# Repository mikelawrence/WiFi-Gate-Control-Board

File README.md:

# WiFi Gate Controller Board

This board performs the same functions as my [WiFi Gate Controller](https://github.com/mikelawrence/WiFi-Gate-Controller), which was designed to add WiFi and Home Assistant control to an existing US Automation Gate Opener board, while providing motor control and standard gate inputs. This board will replace a US Automation Gate Opener board. All inputs are now generalized and also support 10k resistor monitoring for safety devices like edge or photoelectric inputs.

This PCB design uses my custom libraries available here [Mike's KiCad Libraries](https://github.com/mikelawrence/KiCad-Libraries).

This PCB was designed with [KiCad 5.1.4](http://kicad.org).

_Note: Multiple ICs and Modules have exposed pads on the bottom which requires either a reflow oven or hot air to solder properly._

For Bill of Materials generation I use my version of [KiBoM](https://github.com/mikelawrence/KiBoM) forked from [SchrodingersGat](https://github.com/SchrodingersGat/KiBoM).

## Status

* Rev 1.1 PCB was built by and received from PCBWay.
  * This is a 4 layer PCB using 2 oz. copper for all layers and is relatively expensive.
  * Board has been assembled with no problems.
  * Motor interface still needs to be tested everything else is good.
  * You can order PCB from [PCBWay](https://www.pcbway.com/project/shareproject/WiFi_Gate_Control_Board_Rev_1_1.html).
  * You can order parts from Mouser using this [shared BOM](https://www.mouser.com/ProjectManager/ProjectDetail.aspx?AccessID=5c81251866).

* Rev 1.0 PCB was built by and received from PCBWay. Testing is complete.
  * PCBWay built the board.
  * I2C interface to TCA6424A, TCA6408A and LPC5024 verified. Reset not connected error found and corrected in Rev 1.1.
  * 12VDC input and reverse polarity protection verified.
  * LED circuitry and power supply verified.
  * All 12 Inputs verified. This includes switch closure and 10k monitoring.
  * All +12V switched outputs verified. Overload tested also.
  * All 2 Normally Open outputs tested.
  * Full-bridge motor control has been tested up to 30A. Far more than needed.
  * Motor current sensing verified. Removed U26 and connected IN input for each half-bridge directly to processor. Needed to set both half-bridges to active low so MIS offset could be measured unloaded.

## Board Preview

## Design

Intended to replace a US Automatic Patriot Board, this board can directly drive a single gate actuator in both directions. Multiple generic inputs are provided on board to make connection to existing standard gate functionality (open, close, pushbutton...) easy. By providing a WiFi connection to a MQTT server this board can be controlled via standard home automation software (Home Assistant).

Board size is 5.50" X 6.25". This board is smaller than the standard size of a US Automatic Patriot Board but matches existing spacer locations.

### Input Power

The main input connector (J12) provides connections to both the battery and motor. This connector is used by both US Automatic and Apollo gate openers. See pinout below.

A 15 Amp fuse protects the entire board. DC input range is 12V nominal (5V - 17V). Idle input power consumption is pretty variable running from 69mW to 1.38W with an average around 179mW. Peak power is during WiFi transmit.

There are two identical power supplies. U1 powers most of the board via 3.3V. U1's power source is either main power (J12) or the USB connector (J1) so the microprocessor can be programmed on the bench without main power. All LEDs on the board are powered by a separate power supply (U21) which can be turned off by the microprocessor. This substantially reduces power consumption

### Board connections

There are nine screw terminal blocks with removable headers on the board used to connect with all gate functions.

| Terminal | Name  | Conn  | Description                            |
| :---:    | :---: | :---: | :---                                   |
| 01       | +12V  | J3    | +12V power, Always on, fused 0.75A     |
| 02       | IN1   | J3    | Input 1 (Radio)                        |
| 03       | IN2   | J3    | Input 2                                |
| 04       | GND   | J3    | Common Ground                          |
| 05       | +12V  | J5    | +12V power, Always on, fused 0.75A     |
| 06       | IN3   | J5    | Input 3                                |
| 07       | IN4   | J5    | Input 4                                |
| 08       | GND   | J5    | Common Ground                          |
| 09       | IN5   | J8    | Input 5                                |
| 10       | GND   | J8    | Common Ground                          |
| 11       | IN6   | J8    | Input 6                                |
| 12       | GND   | J8    | Common Ground                          |
| 13       | IN7   | J4    | Input 7                                |
| 14       | GND   | J4    | Common Ground                          |
| 15       | IN8   | J4    | Input 8                                |
| 16       | GND   | J4    | Common Ground                          |
| 17       | IN9   | J6    | Input 9                                |
| 18       | GND   | J6    | Common Ground                          |
| 19       | IN10  | J6    | Input 10                               |
| 20       | GND   | J6    | Common Ground                          |
| 21       | IN11  | J7    | +12V power, Switched PhotoEye power    |
| 22       | GND   | J7    | Input 11                               |
| 23       | IN12  | J7    | Input 12                               |
| 24       | GND   | J7    | Common Ground                          |
| 25       | +AL   | J9    | +12V power, Switched Alarm power       |
| 26       | GND   | J9    | Common Ground                          |
| 27       | OUT1  | J7    | Output 1, NO switch Output 1           |
| 28       | COM1  | J7    | Common 1, NO switch Output 1           |
| 29       | GND   | J9    | Common Ground                          |
| 30       | +12V  | J9    | +12V power, Switched Output 1 power    |
| 31       | OUT2  | J7    | Output 2, NO switch Output 2           |
| 32       | COM2  | J7    | Common 2, NO switch Output 2           |
| 33       | GND   | J9    | Common Ground                          |
| 34       | +12V  | J9    | +12V power, Switched Output 2 power    |

### Inputs

There are 12 identical physical inputs on this board. Each input can support Normally Open, Normally Closed, and 10k Monitored Normally Open inputs. A Normally Open input is a dry contact that is open when inactive and closed (shorted) when active. A Normally Closed input is the opposite; closed (shorted) when inactive and open when active. A 10k Monitored input is a Normally Open dry contact with a 8k to 10k resistor across the contacts and is normally used for safety inputs. The resistor allows the connections to the contact to be monitored while inactive. The most current efficient input is the Normally Open input which requires no additional current when inactive. The 10k Monitored input requires an additional 49μA and the Normally Closed input requires a 59μA per input while inactive.

Each input is actually a pair of connections: input and ground (negative terminal of battery). This means the ground side is the same (connected) on all inputs and external wiring must take this into account. Each input can be configured for different gate input types in software as shown in the table below.

| Input          | Other Names                  | Type     | Monitored | Action |
| :---           | :---                         | :---:    | :---:     | :---   |
| Push Button    |                              | NO       | No        | Cycle through Open/Stop/Close commands to gate. |
| Close          |                              | NO       | No        | While active, close gate and holds it closed. |
| Open           | Exit, Free Exit              | NO       | No        | While active, opens gate and holds it open. |
| Stop           |                              | NC       | No        | While active, stops the gate and holds it in position. |
| Open PhotoEye  |                              | NO or NC | Yes       | While active, stops an opening gate or prevents gate from opening. |
| Close PhotoEye |                              | NO or NC | Yes       | While active, reverses a closing gate to full open and holds it open. |
| Safety Edge    |                              | NO       | Yes       | When activated, stops and momentarily reverses a moving gate. |
| Safety Loop    | Reverse Loop                 | NO       | Yes       | While active, reverses a closing gate to full open and holds it open. |
| Shadow Loop    | Center Loop, Under Gate Loop | NO       | Yes       | While active, prevents a closed gate from opening, prevents an open gate from closing, or reverses a closing gate to fully open and holds it open. |
| Input 1        |                              | NO or NC | Yes       | Has no gate function. Can be used to monitor say a mailbox door.
| Input 2        |                              | NO or NC | Yes       | Has no gate function.

Look at [Safety Edge Circuit calculations](drawings/Safety Edge Circuit calculations.pdf) for an explanation of how the input circuits with 10k monitoring work.

### Outputs

There are 4 switched power outputs on the board. J7 is used for PhotoEye connections and thus the +12V is switched on only during gate motion. The Alarm +AL is switched to +12V when alarm is active. The +12V on J10 and J11 output connectors are switched based on output settings.

There are several to be defined output settings here.

### SAMD ARM Processor and WiFi Module

The ARM processor and ATWINC1500 WiFi module are wired identical to the MKR1000 Arduino board, thus the Arduino development environment is used for software development and the ATWINC1500 module is directly supported.

## Setup

### Arduino Setup

This board is designed to mimic a [MKR1000](https://store.arduino.cc/usa/arduino-mkr1000) board from Arduino. Make sure the the MKR1000 board is supported by installing. Do this by opening the Board Manager as shown below.

Type in "samd" in the filter edit and you will see several options. Select "Arduino SAMD Boards (32-bits ARM Cortex-M0+)" and install the latest version as shown below.

It will take a few minutes to download and install the board package. Once complete it's time to install the necessary libraries. Start by opening the Library Manager as shown below.

Type in "mqtt" in the filter edit and scroll down until you see "MQTT by Joel Gaehwiler" as shown below.

Once "MQTT" is installed repeat the install for the following libraries.

* WiFi101 by Arduino
* WiFi101OTA by Arduino
* SD by Arduino
* FreeRTOS_SAMD21 by BriscoeTech
* I2C_DMAC version by Martin Lindupp

### Board Setup

The Arduino development environment expects a bootloader in the SAMD ARM processor which will allow programming via USB. The bootloader must be programmed first using a supported programming pod. I used an "Atmel-ICE" pod but there are other options. First make sure you have selected the "Arduino/Genuino MKR1000" board as shown below.

Next select your programmer.

Make sure the board is powered via USB and the programmer is connected to the debug connector then select "Burn Bootloader".

Now the bootloader is programmed it's time to load the "WiFi101 FirmwareUpdater" example. This will update the firmware in the ATWINC1500 module.

Now "Upload" the "WiFi101 FirmwareUpdater" example.

Update the ATWINC1500 module by selecting "WiFi101 Firmware Updater".

Select the latest WINC1501 Model B firmware and click the "Update Firmware" button.

Finally open the "WiFi_Gate_Controller.ino" sketch downloaded from GitHub. Update the necessary defines for your Wireless network and MQTT server settings see the [Code README](code/README.md) for more information. Now upload it just like the "WiFi101 FirmwareUpdater" example. All done!

This project also supports Visual Studio Code. Visual Studio Code supports building Arduino projects and IntelliSense with code completion. The included settings files support my MacOS environment. Just do a search for "Visual Studio Code Arduino" to see how to install.

## Acknowledgments

* [Arduino](www.arduino.cc) kindly develops open source hardware and software which makes writing software for this board and especially the WiFi module easy.
* [Visual Studio Code](https://code.visualstudio.com/) from Microsoft is a great alternative to the Arduino IDE.

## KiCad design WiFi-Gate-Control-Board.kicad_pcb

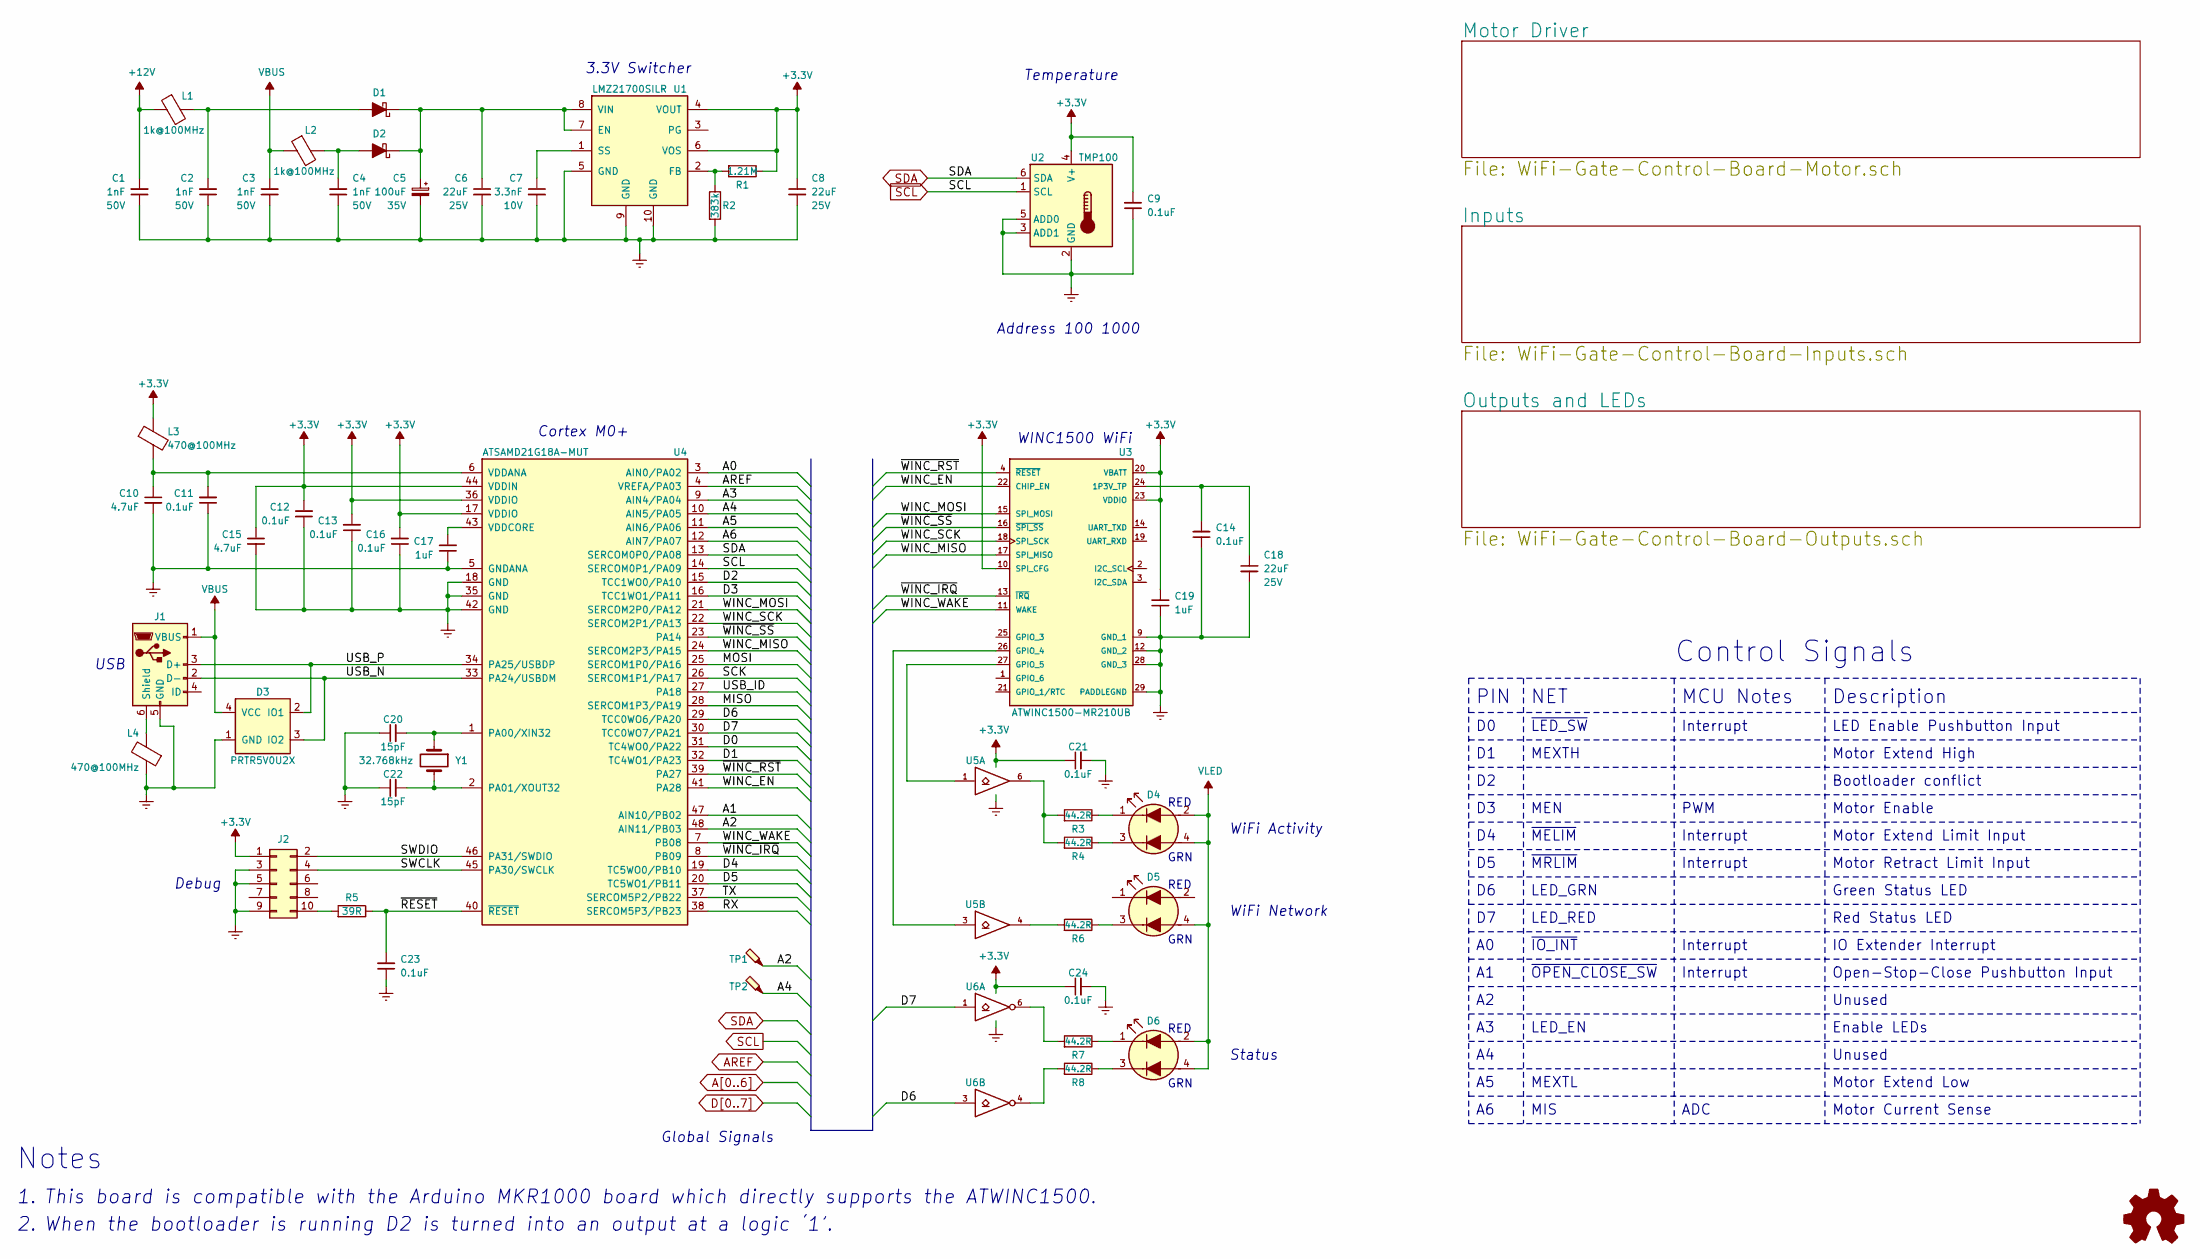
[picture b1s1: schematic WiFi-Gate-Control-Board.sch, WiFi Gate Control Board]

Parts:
C1, C2, C3, C4: 1nF; C_0603_1608Metric; Voltage 50V; Tolerance 10%; Part Number VJ0603Y102KXAAC31
C5: 100uF; CP_Elec_8x10; Voltage 35V; Tolerance 20%; Part Number EMVH350ADA101MHA0G
C6, C8, C18: 22uF; C_0805_2012Metric; Voltage 25V; Tolerance 20%; Part Number TMK212BBJ226MG-TT
C7: 3.3nF; C_0603_1608Metric; Voltage 10V; Tolerance 5%; Part Number VJ0603Y332JXQPW1BC
C9, C11, C12, C13, C14, C16, C21, C23, C24: 0.1uF; C_0603_1608Metric; Voltage 50V; Tolerance 5%; Part Number CC603JRX7R9BB104
C10, C15: 4.7uF; C_0603_1608Metric; Voltage 6.3V; Tolerance 10%; Part Number JMK107BB7475KA-T
C17, C19: 1uF; C_0603_1608Metric; Voltage 50V; Tolerance 10%; Part Number UMK107BJ105KA-T
C20, C22: 15pF; C_0603_1608Metric; Voltage 50V; Tolerance 5%; Part Number 06035A150JAT2A
D1, D2: DFLS130; D_PowerDI-123; Part Number DFLS130LQ
D3: PRTR5V0U2X; SOT-143; Part Number PRTR5V0U2X,215
D4, D5, D6: Red/Green; LED_Avago_PLCC4_3.2x2.8mm_CW; Part Number HSMF-A203-A00J1
J1: USB_B_Micro; USB_Micro-B_Wuerth_614105150721_Vertical_CircularHoles; Part Number 614105150721
J2: Cortex Debug; PinHeader_2x05_P1.27mm_Vertical_SMD; Part Number FTSH-105-01-L-DV-K
L1, L2: 1k@100MHz; L_1206_3216Metric; Part Number BLM31KN102SH1L
L3, L4: 470@100MHz; L_0603_1608Metric; Part Number BLM18PG471SN1D
R1: 1.21M; R_0603_1608Metric; Tolerance 1%; Part Number RC0603FR-071M21L
R2: 383k; R_0603_1608Metric; Tolerance 1%; Part Number ERJ-3EKF3833V
R3, R4, R6, R7, R8: 44.2R; R_0603_1608Metric; Tolerance 1%; Part Number ERJ-3EKF44R2V
R5: 39R; R_0603_1608Metric; Tolerance 1%; Part Number ERJ-3EKF39R0V
TP1, TP2: TestPoint_Probe; TestPoint_Pad_D1.0mm
U1: LMZ21700; Converter_DCDC_Texas-SIL0008E; Part Number LMZ21700SILR
U2: TMP100; SOT-23-6; Part Number TMP100AQDBVRQ1
U3: ATWINC1500-MR210UB; Microchip_ATWINC1500-MR210UB; Part Number ATWINC1500-MR210UB1140
U4: SAMD21G18-M; QFN-48-1EP_7x7mm_P0.5mm_EP5.15x5.15mm; Part Number ATSAMD21G18A-MUT
U5: 74LVC2G07; SOT-23-6; Part Number SN74LVC2G07DBVR
U6: 74LVC2G06; SOT-23-6; Part Number SN74LVC2G06DBVR
Y1: 32.768kHz; Crystal_SMD_Abracon_ABS07-2Pin_3.2x1.5mm; Part Number ABS07-32.768KHZ-9-T

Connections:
+3.3V: C8.1, C9.2, C12.2, C13.2, C15.1, C16.2, C19.2, C21.1, C24.1, J2.1, L3.1, R1.1, U1.4 (VOUT), U1.6 (VOS), U2.4 (V+), U3.10 (SPI_CFG), U3.20 (VBATT), U3.23 (VDDIO), U4.17 (VDDIO), U4.36 (VDDIO), U4.44 (VDDIN), U5.5 (VCC), U6.5 (VCC); also elsewhere on the board
+12V: C1.2, L1.1; also elsewhere on the board
/SWCLK: J2.4, U4.45 (PA30/SWCLK)
/SWDIO: J2.2, U4.46 (PA31/SWDIO)
/USB_N: D3.3 (IO2), J1.2 (D-), U4.33 (PA24/USBDM)
/USB_P: D3.2 (IO1), J1.3 (D+), U4.34 (PA25/USBDP)
/WINC_EN: U3.22 (CHIP_EN), U4.41 (PA28)
/WINC_MISO: U3.17 (SPI_MISO), U4.24 (SERCOM2P3/PA15)
/WINC_MOSI: U3.15 (SPI_MOSI), U4.21 (SERCOM2P0/PA12)
/WINC_SCK: U3.18 (SPI_SCK), U4.22 (SERCOM2P1/PA13)
/WINC_WAKE: U3.11 (WAKE), U4.7 (PB08)
/~RESET~: C23.2, R5.1, U4.40 (~RESET~)
/~WINC_IRQ: U3.13 (~IRQ~), U4.8 (PB09)
/~WINC_RST: U3.4 (~RESET~), U4.39 (PA27)
/~WINC_SS: U3.16 (~SPI_SS~), U4.23 (PA14)
A0: U4.3 (AIN0/PA02); also elsewhere on the board
A1: U4.47 (AIN10/PB02); also elsewhere on the board
A2: TP1.1, U4.48 (AIN11/PB03)
A3: U4.9 (AIN4/PA04); also elsewhere on the board
A4: TP2.1, U4.10 (AIN5/PA05)
A5: U4.11 (AIN6/PA06); also elsewhere on the board
A6: U4.12 (AIN7/PA07); also elsewhere on the board
AREF: U4.4 (VREFA/PA03); also elsewhere on the board
D0: U4.31 (TC4WO0/PA22); also elsewhere on the board
D1: U4.32 (TC4WO1/PA23); also elsewhere on the board
D3: U4.16 (TCC1WO1/PA11); also elsewhere on the board
D4: U4.19 (TC5WO0/PB10); also elsewhere on the board
D5: U4.20 (TC5WO1/PB11); also elsewhere on the board
D6: U4.29 (TCC0WO6/PA20), U6.3
D7: U4.30 (TCC0WO7/PA21), U6.1
GND: C1.1, C2.1, C3.1, C4.1, C5.2, C6.2, C7.2, C8.2, C9.1, C10.2, C11.1, C12.1, C13.1, C14.1, C15.2, C16.1, C17.1, C18.2, C19.1, C20.1, C21.2, C22.1, C23.1, C24.2, D3.1 (GND), J1.5 (GND), J2.3, J2.5, J2.9, L4.1, R2.2, U1.5 (GND), U1.9 (GND), U1.10 (GND), U2.2 (GND), U2.3 (ADD1), U2.5 (ADD0), U3.9 (GND_1), U3.12 (GND_2), U3.28 (GND_3), U3.29 (PADDLEGND), U4.5 (GNDANA), U4.18 (GND), U4.35 (GND), U4.42 (GND), U5.2 (GND), U6.2 (GND); also elsewhere on the board
unnamed: C2.2, D1.2 (A), L1.2
unnamed: C4.2, D2.2 (A), L2.2
unnamed: C5.1, C6.1, D1.1 (K), D2.1 (K), U1.7 (EN), U1.8 (VIN)
unnamed: C7.1, U1.1 (SS)
unnamed: C10.1, C11.2, L3.2, U4.6 (VDDANA)
unnamed: C14.2, C18.1, U3.24 (1P3V_TP)
unnamed: C17.2, U4.43 (VDDCORE)
unnamed: C20.2, U4.1 (PA00/XIN32), Y1.1
unnamed: C22.2, U4.2 (PA01/XOUT32), Y1.2
unnamed: D4.1 (K1), R3.1
unnamed: D4.3 (K2), R4.1
unnamed: D5.3 (K2), R6.1
unnamed: D6.1 (K1), R7.1
unnamed: D6.3 (K2), R8.1
unnamed: J1.6 (Shield), L4.2
unnamed: J2.10, R5.2
unnamed: R1.2, R2.1, U1.2 (FB)
unnamed: R3.2, R4.2, U5.6
unnamed: R6.2, U5.4
unnamed: R7.2, U6.6
unnamed: R8.2, U6.4
unnamed: U3.26 (GPIO_4), U5.3
unnamed: U3.27 (GPIO_5), U5.1
SCL: U2.1 (SCL), U4.14 (SERCOM0P1/PA09); also elsewhere on the board
SDA: U2.6 (SDA), U4.13 (SERCOM0P0/PA08); also elsewhere on the board
VBUS: C3.2, D3.4 (VCC), J1.1 (VBUS), L2.1
VLED: D4.2 (A1), D4.4 (A2), D5.4 (A2), D6.2 (A1), D6.4 (A2); also elsewhere on the board

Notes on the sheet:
3.3V Switcher
Temperature
This board is compatible with the Arduino MKR1000 board which directly supports the ATWINC1500.
Debug
USB
Cortex M0+
WINC1500 WiFi
When the bootloader is running D2 is turned into an output at a logic ‘1’.
Global Signals
Status
RED
GRN
WiFi Activity
WiFi Network
~OPEN_CLOSE_SW
Open-Stop-Close Pushbutton Input
~IO_INT
IO Extender Interrupt
~MELIM
Motor Extend Limit Input
LED_GRN
Green Status LED
LED_RED
Red Status LED
Motor Current Sense
MEXTH
Motor Extend High
PIN
NET
Description
Bootloader conflict
Control Signals
LED_EN
Enable LEDs
MCU Notes
Interrupt
ADC
Motor Extend Low
MIS
LED Enable Pushbutton Input

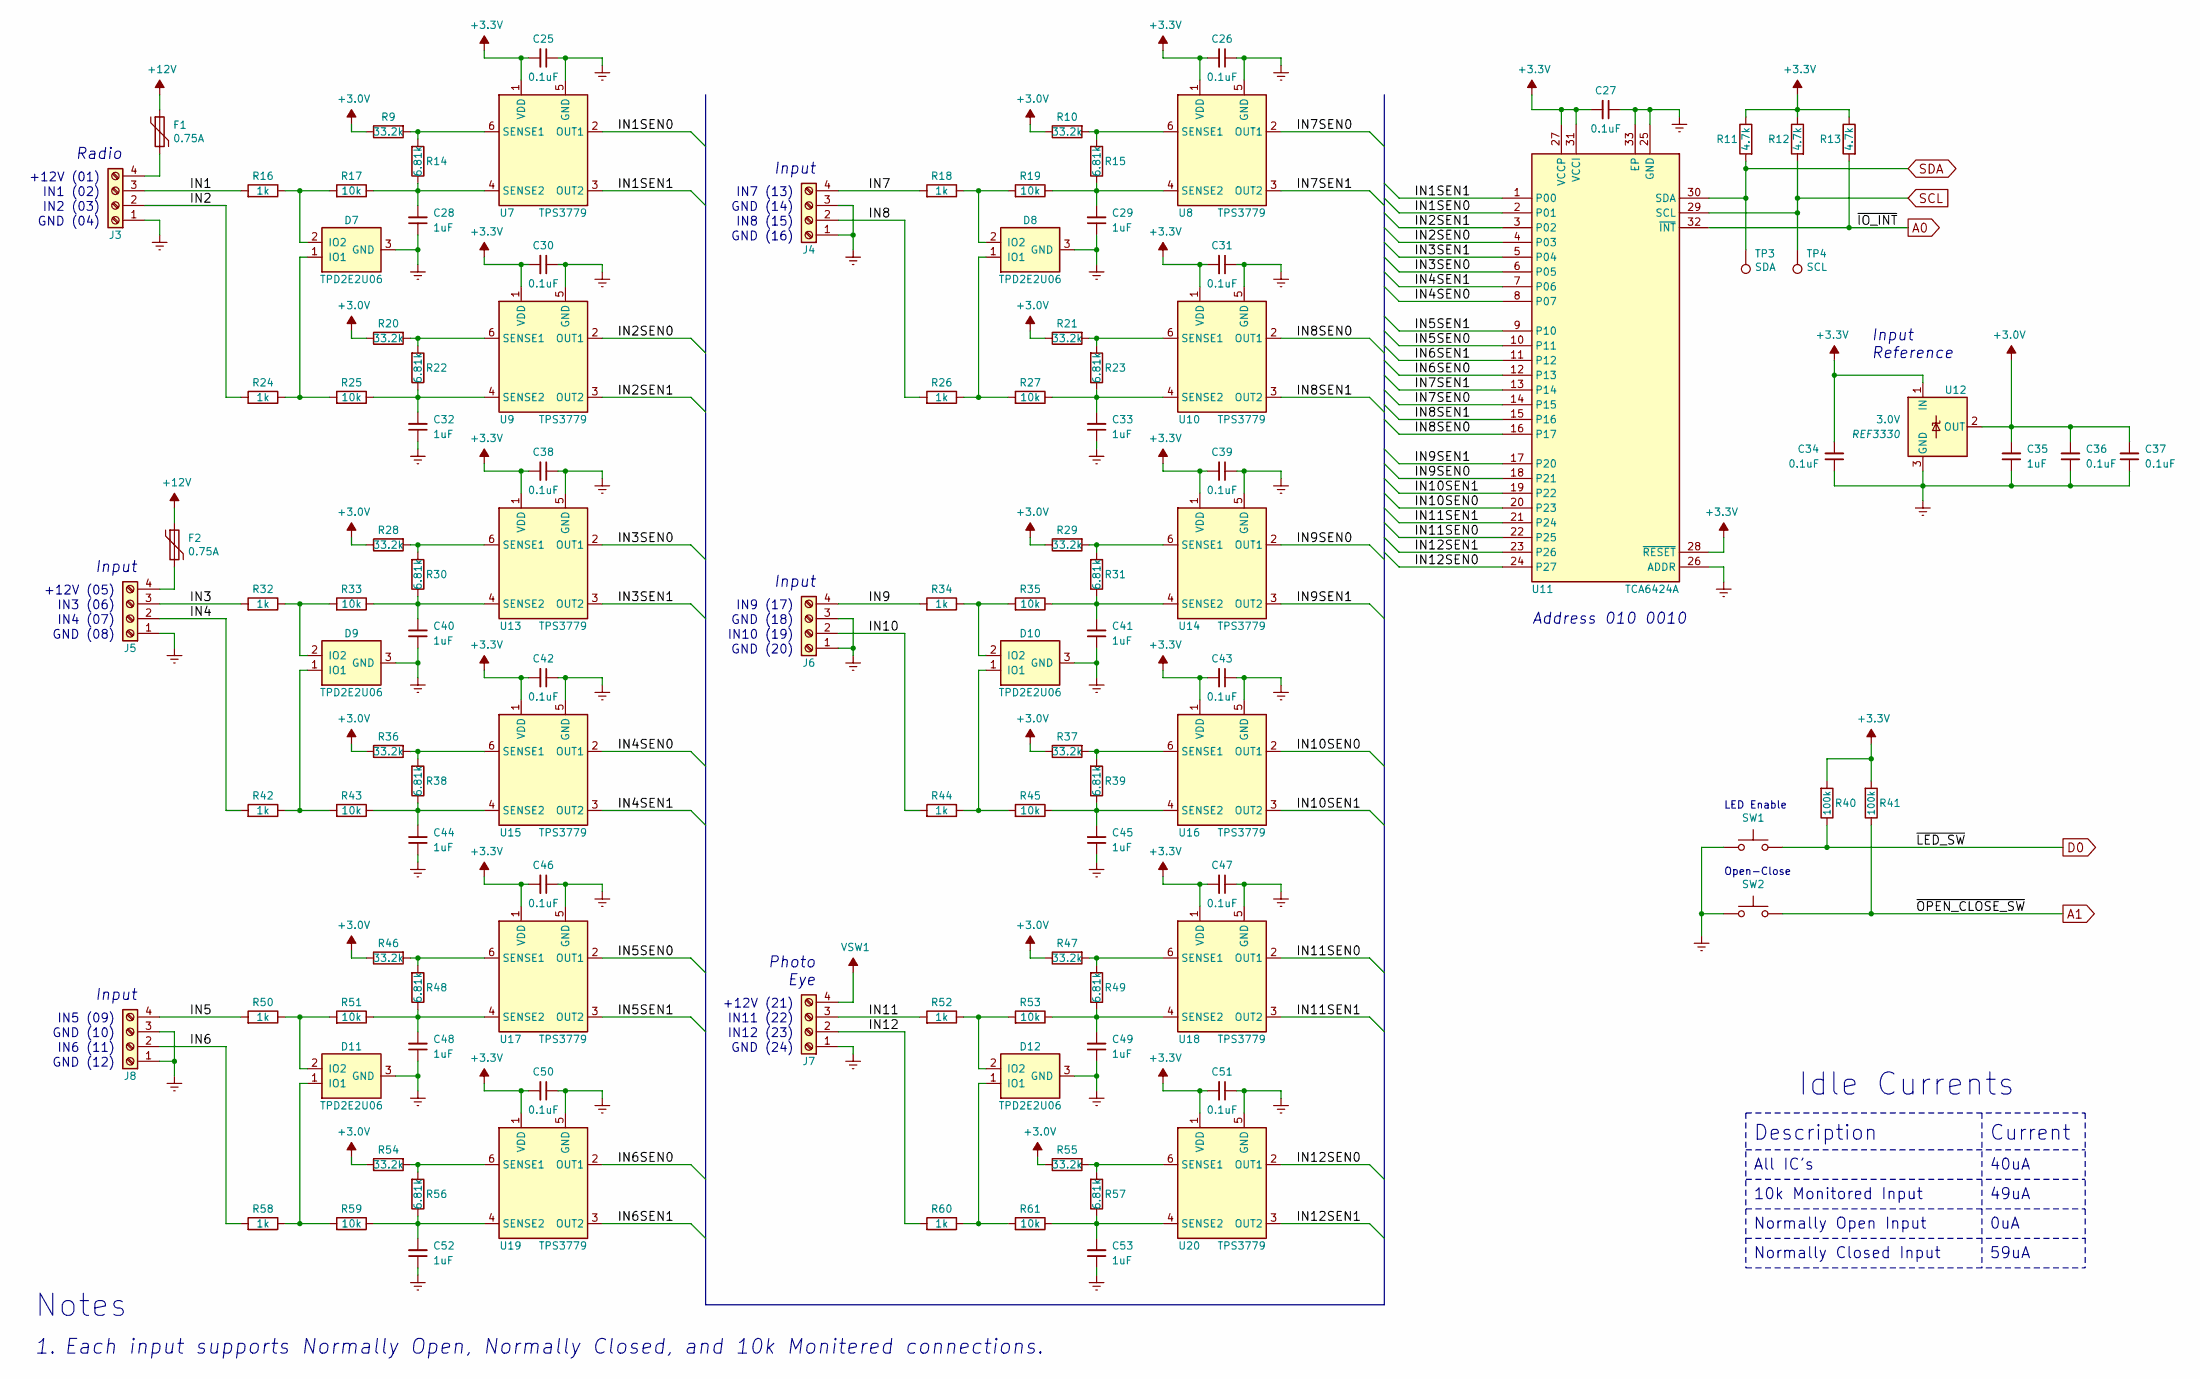
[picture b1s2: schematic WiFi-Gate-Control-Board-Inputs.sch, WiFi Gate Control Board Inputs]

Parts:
C25, C26, C27, C30, C31, C34, C36, C37, C38, C39, C42, C43, C46, C47, C50, C51: 0.1uF; C_0603_1608Metric; Voltage 50V; Tolerance 5%; Part Number CC603JRX7R9BB104
C28, C29, C32, C33, C35, C40, C41, C44, C45, C48, C49, C52, C53: 1uF; C_0603_1608Metric; Voltage 50V; Tolerance 10%; Part Number UMK107BJ105KA-T
D7, D8, D9, D10, D11, D12: TPD2E2U06; SOT-323_SC-70; Part Number TPD2E2U06QDCKRQ1
F1, F2: 0.75A; Fuse_Bourns_MF-SM_7.98x5.44mm; Part Number MFSM075-2
J3, J4, J5, J6, J7, J8: Screw Header 4 Pos; PhoenixContact_MSTBVA_2,5_4-G-5,08_1x04_P5.08mm_Vertical; Part Number 1755752
R9, R10, R20, R21, R28, R29, R36, R37, R46, R47, R54, R55: 33.2k; R_0603_1608Metric; Tolerance 0.5%; Part Number RR0816P-3322D51C
R11, R12, R13: 4.7k; R_0603_1608Metric; Tolerance 1%; Part Number ERJ-3EKF4701V
R14, R15, R22, R23, R30, R31, R38, R39, R48, R49, R56, R57: 6.81k; R_0603_1608Metric; Tolerance 0.5%; Part Number RR0816P-6811D81H
R16, R18, R24, R26, R32, R34, R42, R44, R50, R52, R58, R60: 1k; R_1206_3216Metric; Tolerance 0.5%; Part Number AC1206DR-071KL
R17, R19, R25, R27, R33, R35, R43, R45, R51, R53, R59, R61: 10k; R_0603_1608Metric; Tolerance 0.5%; Part Number RR0816P-103-D
R40, R41: 100k; R_0603_1608Metric; Tolerance 1%; Part Number ERJ-3EKF1003V
SW1, SW2: SW_PUSH-12mm_Wuerth-430476085716; Part Number 430476085716
TP3: SDA; TestPoint_THTPad_D1.5mm_Drill0.7mm
TP4: SCL; TestPoint_THTPad_D1.5mm_Drill0.7mm
U7, U8, U9, U10, U13, U14, U15, U16, U17, U18, U19, U20: TPS3779; SOT-23-6; Part Number TPS3779BDBVR
U11: TCA6424A; VQFN-32-1EP_5x5mm_P0.5mm_EP3.1x3.1mm_ThermalVias; Part Number TCA6424ARGJR
U12: REF3330; SOT-23; Voltage 3.0V; Part Number REF3330AIDBZR

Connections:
+3.0V: C35.2, C36.2, C37.2, R9.1, R10.1, R20.1, R21.1, R28.1, R29.1, R36.1, R37.1, R46.1, R47.1, R54.1, R55.1, U12.2 (OUT)
+3.3V: C25.2, C26.2, C27.2, C30.2, C31.2, C34.2, C38.2, C39.2, C42.2, C43.2, C46.2, C47.2, C50.2, C51.2, R11.1, R12.1, R13.1, R40.2, R41.2, U7.1 (VDD), U8.1 (VDD), U9.1 (VDD), U10.1 (VDD), U11.27 (VCCP), U11.28 (~RESET), U11.31 (VCCI), U12.1 (IN), U13.1 (VDD), U14.1 (VDD), U15.1 (VDD), U16.1 (VDD), U17.1 (VDD), U18.1 (VDD), U19.1 (VDD), U20.1 (VDD); also elsewhere on the board
+12V: F1.1, F2.1; also elsewhere on the board
/Inputs/IN1: J3.3, R16.2
/Inputs/IN1SEN0: U7.2 (OUT1), U11.2 (P01)
/Inputs/IN1SEN1: U7.3 (OUT2), U11.1 (P00)
/Inputs/IN2: J3.2, R24.2
/Inputs/IN2SEN0: U9.2 (OUT1), U11.4 (P03)
/Inputs/IN2SEN1: U9.3 (OUT2), U11.3 (P02)
/Inputs/IN3: J5.3, R32.2
/Inputs/IN3SEN0: U11.6 (P05), U13.2 (OUT1)
/Inputs/IN3SEN1: U11.5 (P04), U13.3 (OUT2)
/Inputs/IN4: J5.2, R42.2
/Inputs/IN4SEN0: U11.8 (P07), U15.2 (OUT1)
/Inputs/IN4SEN1: U11.7 (P06), U15.3 (OUT2)
/Inputs/IN5: J8.4, R50.2
/Inputs/IN5SEN0: U11.10 (P11), U17.2 (OUT1)
/Inputs/IN5SEN1: U11.9 (P10), U17.3 (OUT2)
/Inputs/IN6: J8.2, R58.2
/Inputs/IN6SEN0: U11.12 (P13), U19.2 (OUT1)
/Inputs/IN6SEN1: U11.11 (P12), U19.3 (OUT2)
/Inputs/IN7: J4.4, R18.2
/Inputs/IN7SEN0: U8.2 (OUT1), U11.14 (P15)
/Inputs/IN7SEN1: U8.3 (OUT2), U11.13 (P14)
/Inputs/IN8: J4.2, R26.2
/Inputs/IN8SEN0: U10.2 (OUT1), U11.16 (P17)
/Inputs/IN8SEN1: U10.3 (OUT2), U11.15 (P16)
/Inputs/IN9: J6.4, R34.2
/Inputs/IN9SEN0: U11.18 (P21), U14.2 (OUT1)
/Inputs/IN9SEN1: U11.17 (P20), U14.3 (OUT2)
/Inputs/IN10: J6.2, R44.2
/Inputs/IN10SEN0: U11.20 (P23), U16.2 (OUT1)
/Inputs/IN10SEN1: U11.19 (P22), U16.3 (OUT2)
/Inputs/IN11: J7.3, R52.2
/Inputs/IN11SEN0: U11.22 (P25), U18.2 (OUT1)
/Inputs/IN11SEN1: U11.21 (P24), U18.3 (OUT2)
/Inputs/IN12: J7.2, R60.2
/Inputs/IN12SEN0: U11.24 (P27), U20.2 (OUT1)
/Inputs/IN12SEN1: U11.23 (P26), U20.3 (OUT2)
A0: R13.2, U11.32 (~INT); also elsewhere on the board
A1: R41.1, SW2.2; also elsewhere on the board
D0: R40.1, SW1.2; also elsewhere on the board
GND: C25.1, C26.1, C27.1, C28.1, C29.1, C30.1, C31.1, C32.1, C33.1, C34.1, C35.1, C36.1, C37.1, C38.1, C39.1, C40.1, C41.1, C42.1, C43.1, C44.1, C45.1, C46.1, C47.1, C48.1, C49.1, C50.1, C51.1, C52.1, C53.1, D7.3 (GND), D8.3 (GND), D9.3 (GND), D10.3 (GND), D11.3 (GND), D12.3 (GND), J3.1, J4.1, J4.3, J5.1, J6.1, J6.3, J7.1, J8.1, J8.3, SW1.1, SW2.1, U7.5 (GND), U8.5 (GND), U9.5 (GND), U10.5 (GND), U11.25 (GND), U11.26 (ADDR), U11.33 (EP), U12.3 (GND), U13.5 (GND), U14.5 (GND), U15.5 (GND), U16.5 (GND), U17.5 (GND), U18.5 (GND), U19.5 (GND), U20.5 (GND); also elsewhere on the board
unnamed: C28.2, R14.1, R17.1, U7.4 (SENSE2)
unnamed: C29.2, R15.1, R19.1, U8.4 (SENSE2)
unnamed: C32.2, R22.1, R25.1, U9.4 (SENSE2)
unnamed: C33.2, R23.1, R27.1, U10.4 (SENSE2)
unnamed: C40.2, R30.1, R33.1, U13.4 (SENSE2)
unnamed: C41.2, R31.1, R35.1, U14.4 (SENSE2)
unnamed: C44.2, R38.1, R43.1, U15.4 (SENSE2)
unnamed: C45.2, R39.1, R45.1, U16.4 (SENSE2)
unnamed: C48.2, R48.1, R51.1, U17.4 (SENSE2)
unnamed: C49.2, R49.1, R53.1, U18.4 (SENSE2)
unnamed: C52.2, R56.1, R59.1, U19.4 (SENSE2)
unnamed: C53.2, R57.1, R61.1, U20.4 (SENSE2)
unnamed: D7.1 (IO1), R24.1, R25.2
unnamed: D7.2 (IO2), R16.1, R17.2
unnamed: D8.1 (IO1), R26.1, R27.2
unnamed: D8.2 (IO2), R18.1, R19.2
unnamed: D9.1 (IO1), R42.1, R43.2
unnamed: D9.2 (IO2), R32.1, R33.2
unnamed: D10.1 (IO1), R44.1, R45.2
unnamed: D10.2 (IO2), R34.1, R35.2
unnamed: D11.1 (IO1), R58.1, R59.2
unnamed: D11.2 (IO2), R50.1, R51.2
unnamed: D12.1 (IO1), R60.1, R61.2
unnamed: D12.2 (IO2), R52.1, R53.2
unnamed: F1.2, J3.4
unnamed: F2.2, J5.4
unnamed: R10.2, R15.2, U8.6 (SENSE1)
unnamed: R9.2, R14.2, U7.6 (SENSE1)
unnamed: R20.2, R22.2, U9.6 (SENSE1)
unnamed: R21.2, R23.2, U10.6 (SENSE1)
unnamed: R28.2, R30.2, U13.6 (SENSE1)
unnamed: R29.2, R31.2, U14.6 (SENSE1)
unnamed: R36.2, R38.2, U15.6 (SENSE1)
unnamed: R37.2, R39.2, U16.6 (SENSE1)
unnamed: R46.2, R48.2, U17.6 (SENSE1)
unnamed: R47.2, R49.2, U18.6 (SENSE1)
unnamed: R54.2, R56.2, U19.6 (SENSE1)
unnamed: R55.2, R57.2, U20.6 (SENSE1)
SCL: R12.2, TP4.1, U11.29 (SCL); also elsewhere on the board
SDA: R11.2, TP3.1, U11.30 (SDA); also elsewhere on the board
VSW1: J7.4; also elsewhere on the board

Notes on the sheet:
Radio
Address 010 0010
Photo Eye
Each input supports Normally Open, Normally Closed, and 10k Monitered connections.
+12V (01)
IN1 (02)
IN2 (03)
GND (04)
+12V (05)
IN3 (06)
GND (08)
GND (10)
GND (12)
IN4 (07)
IN5 (09)
IN6 (11)
GND (14)
IN7 (13)
GND (16)
IN8 (15)
GND (18)
IN9 (17)
GND (20)
IN10 (19)
+12V (21)
IN11 (22)
IN12 (23)
GND (24)
Input
Input Reference
All IC’s
Description
10k Monitored Input
Normally Open Input
Current
40uA
0uA
49uA
Idle Currents
Normally Closed Input

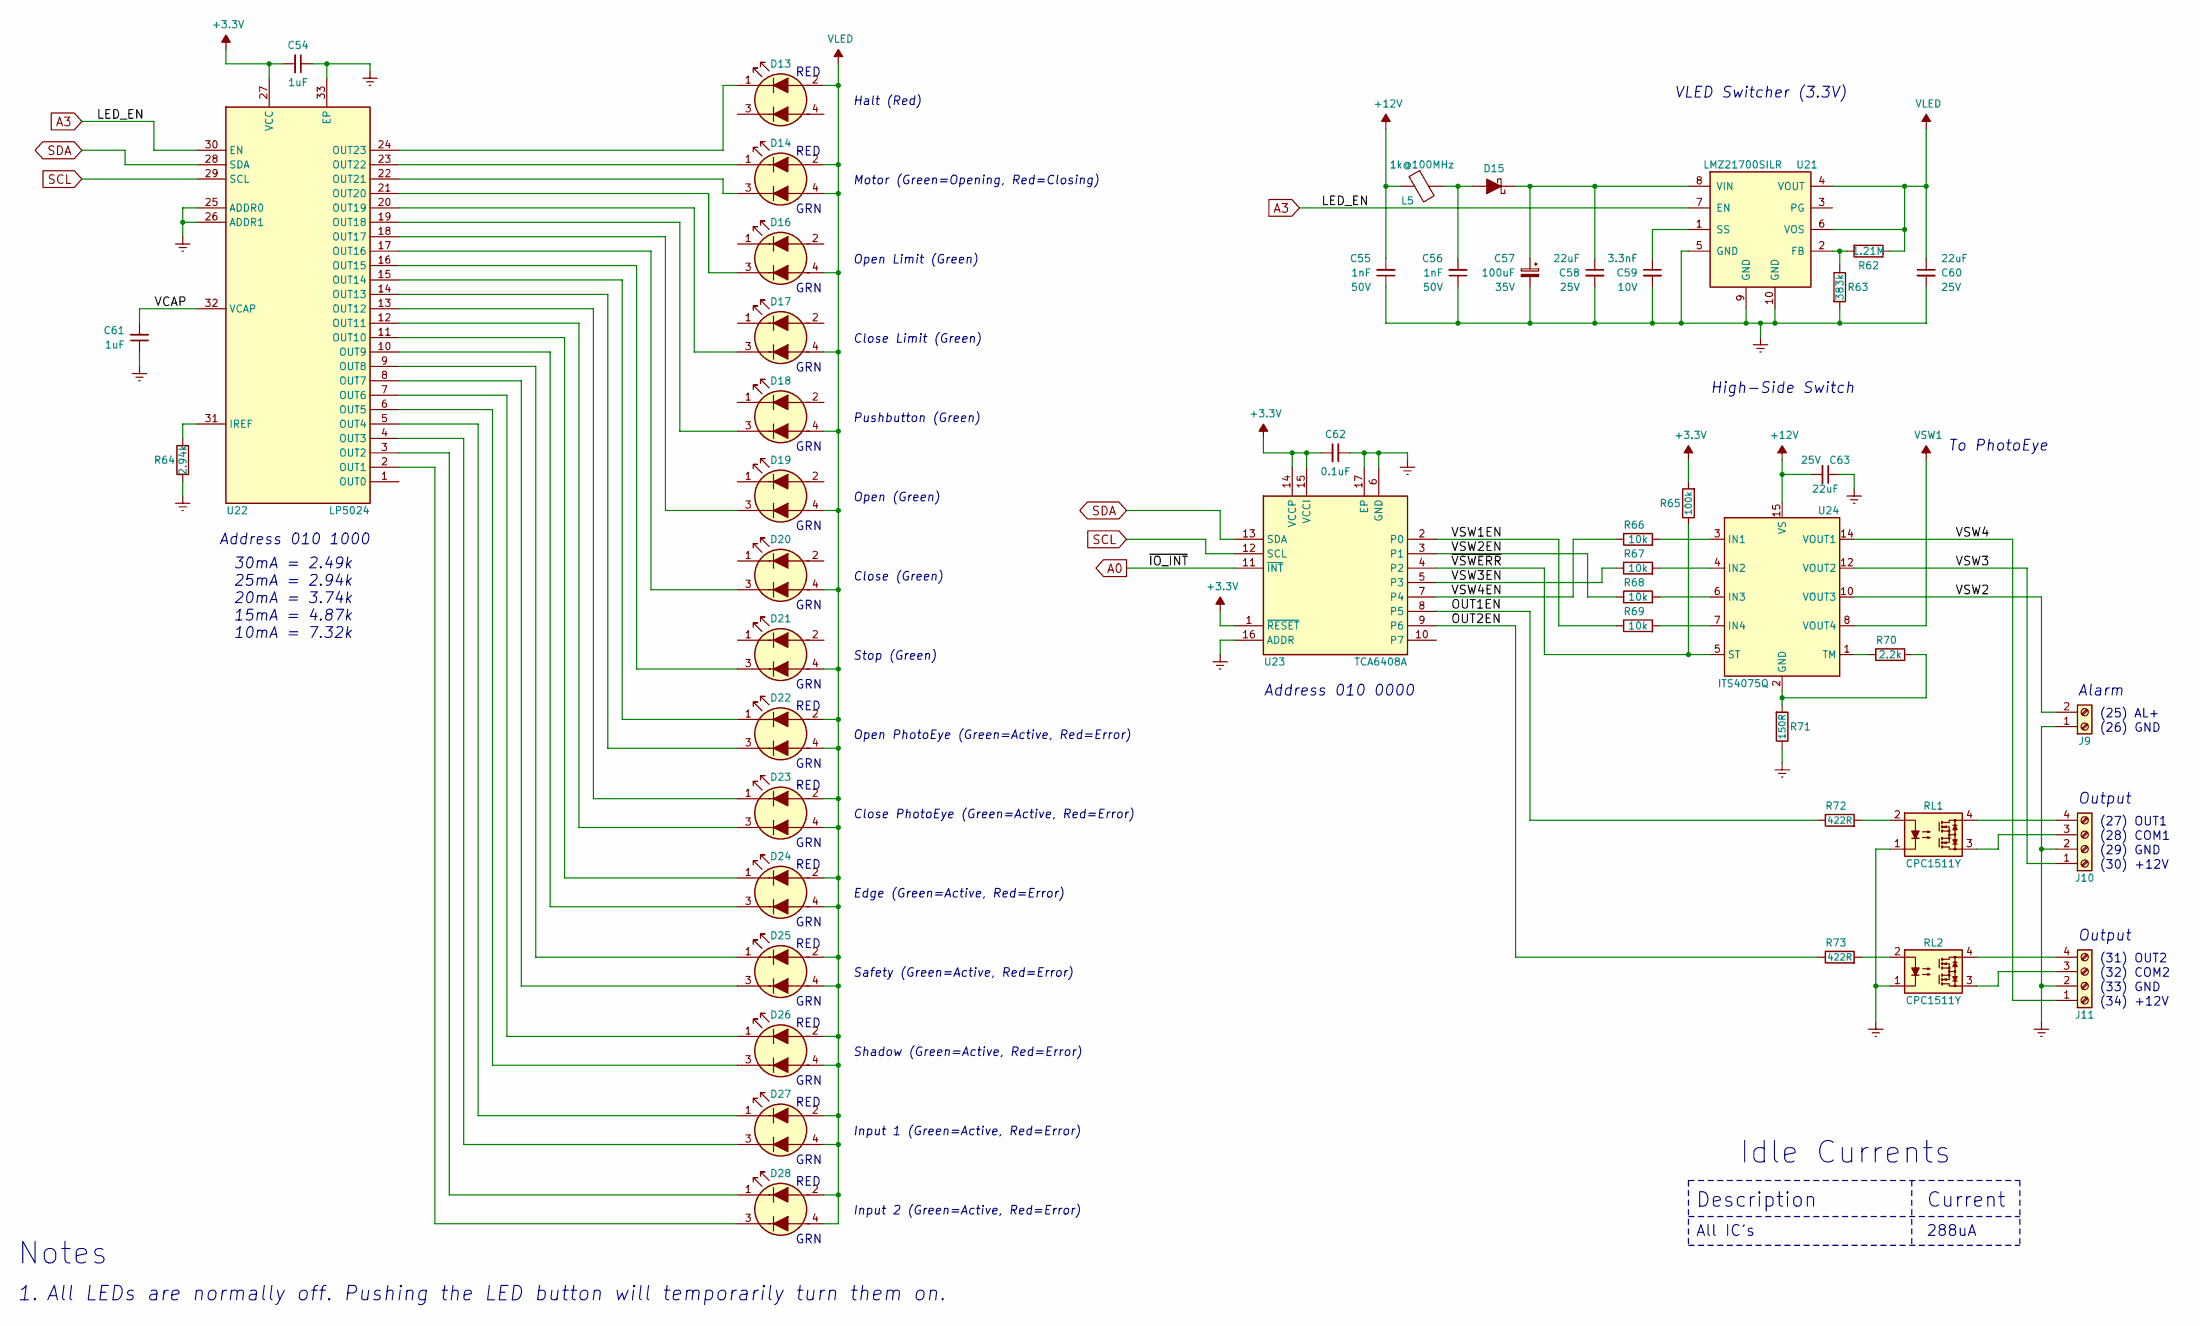
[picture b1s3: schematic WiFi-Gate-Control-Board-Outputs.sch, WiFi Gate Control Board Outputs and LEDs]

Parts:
C54, C61: 1uF; C_0603_1608Metric; Voltage 50V; Tolerance 10%; Part Number UMK107BJ105KA-T
C55, C56: 1nF; C_0603_1608Metric; Voltage 50V; Tolerance 10%; Part Number VJ0603Y102KXAAC31
C57: 100uF; CP_Elec_8x10; Voltage 35V; Tolerance 20%; Part Number EMVH350ADA101MHA0G
C58, C60, C63: 22uF; C_0805_2012Metric; Voltage 25V; Tolerance 20%; Part Number TMK212BBJ226MG-TT
C59: 3.3nF; C_0603_1608Metric; Voltage 10V; Tolerance 5%; Part Number VJ0603Y332JXQPW1BC
C62: 0.1uF; C_0603_1608Metric; Voltage 50V; Tolerance 5%; Part Number CC603JRX7R9BB104
D13, D14, D16, D17, D18, D19, D20, D21, D22, D23, D24, D25, D26, D27, D28: Red/Green; LED_Avago_PLCC4_3.2x2.8mm_CW; Part Number HSMF-A203-A00J1
D15: DFLS130; D_PowerDI-123; Part Number DFLS130LQ
J9: Screw Header 2 Pos; PhoenixContact_MSTBVA_2,5_2-G-5,08_1x02_P5.08mm_Vertical; Part Number 1755736
J10, J11: Screw Header 4 Pos; PhoenixContact_MSTBVA_2,5_4-G-5,08_1x04_P5.08mm_Vertical; Part Number 1755752
L5: 1k@100MHz; L_1206_3216Metric; Part Number BLM31KN102SH1L
R62: 1.21M; R_0603_1608Metric; Tolerance 1%; Part Number RC0603FR-071M21L
R63: 383k; R_0603_1608Metric; Tolerance 1%; Part Number ERJ-3EKF3833V
R64: 2.94k; R_0603_1608Metric; Tolerance 1%; Part Number ERJ-3EKF2941V
R65: 100k; R_0603_1608Metric; Tolerance 1%; Part Number ERJ-3EKF1003V
R66, R67, R68, R69: 10k; R_0603_1608Metric; Tolerance 0.5%; Part Number RR0816P-103-D
R70: 2.2k; R_0603_1608Metric; Tolerance 1%; Part Number ERJ-3EKF2201V
R71: 150R; R_1218_3246Metric; Tolerance 1%; Part Number CRCW1218150RFKEK
R72, R73: 422R; R_0603_1608Metric; Tolerance 1%; Part Number ERJ-3EKF4220V
RL1, RL2: CPC1511Y; Relay_IXYS_PowerSIP; Part Number CPC1511Y
U21: LMZ21700; Converter_DCDC_Texas-SIL0008E; Part Number LMZ21700SILR
U22: LP5024; QFN-32-1EP_4x4mm_P0.4mm_EP2.9x2.9mm_ThermalVias; Part Number LP5024RSMR
U23: TCA6408A; VQFN-16-1EP_3x3mm_P0.5mm_EP1.45x1.45mm_ThermalVias; Part Number TCA6408ARGTR
U24: ITS4075Q; Infineon_PG-TSDSO-14-22; Part Number ITS4075Q-EP-DXUMA1

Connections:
+3.3V: C54.2, C62.2, R65.2, U22.27 (VCC), U23.1 (~RESET), U23.14 (VCCP), U23.15 (VCCI); also elsewhere on the board
+12V: C55.2, C63.2, L5.1, U24.15 (VS); also elsewhere on the board
/Outputs and LEDs/OUT1EN: R72.1, U23.8 (P5)
/Outputs and LEDs/OUT2EN: R73.1, U23.9 (P6)
/Outputs and LEDs/VCAP: C61.2, U22.32 (VCAP)
/Outputs and LEDs/VSW1EN: R69.1, U23.2 (P0)
/Outputs and LEDs/VSW2: J9.2, U24.10 (VOUT3)
/Outputs and LEDs/VSW2EN: R68.1, U23.3 (P1)
/Outputs and LEDs/VSW3: J10.1, U24.12 (VOUT2)
/Outputs and LEDs/VSW3EN: R67.1, U23.5 (P3)
/Outputs and LEDs/VSW4: J11.1, U24.14 (VOUT1)
/Outputs and LEDs/VSW4EN: R66.1, U23.7 (P4)
/Outputs and LEDs/~VSWERR: R65.1, U23.4 (P2), U24.5 (ST)
A0: U23.11 (~INT); also elsewhere on the board
A3: U21.7 (EN), U22.30 (EN); also elsewhere on the board
GND: C54.1, C55.1, C56.1, C57.2, C58.2, C59.2, C60.2, C61.1, C62.1, C63.1, J9.1, J10.2, J11.2, R63.2, R64.1, R71.1, RL1.1, RL2.1, U21.5 (GND), U21.9 (GND), U21.10 (GND), U22.25 (ADDR0), U22.26 (ADDR1), U22.33 (EP), U23.6 (GND), U23.16 (ADDR), U23.17 (EP); also elsewhere on the board
unnamed: C56.2, D15.2 (A), L5.2
unnamed: C57.1, C58.1, D15.1 (K), U21.8 (VIN)
unnamed: C59.1, U21.1 (SS)
unnamed: D13.1 (K1), U22.24 (OUT23)
unnamed: D14.1 (K1), U22.23 (OUT22)
unnamed: D14.3 (K2), U22.22 (OUT21)
unnamed: D16.3 (K2), U22.21 (OUT20)
unnamed: D17.3 (K2), U22.20 (OUT19)
unnamed: D18.3 (K2), U22.19 (OUT18)
unnamed: D19.3 (K2), U22.18 (OUT17)
unnamed: D20.3 (K2), U22.17 (OUT16)
unnamed: D21.3 (K2), U22.16 (OUT15)
unnamed: D22.1 (K1), U22.15 (OUT14)
unnamed: D22.3 (K2), U22.14 (OUT13)
unnamed: D23.1 (K1), U22.13 (OUT12)
unnamed: D23.3 (K2), U22.12 (OUT11)
unnamed: D24.1 (K1), U22.11 (OUT10)
unnamed: D24.3 (K2), U22.10 (OUT9)
unnamed: D25.1 (K1), U22.9 (OUT8)
unnamed: D25.3 (K2), U22.8 (OUT7)
unnamed: D26.1 (K1), U22.7 (OUT6)
unnamed: D26.3 (K2), U22.6 (OUT5)
unnamed: D27.1 (K1), U22.5 (OUT4)
unnamed: D27.3 (K2), U22.4 (OUT3)
unnamed: D28.1 (K1), U22.3 (OUT2)
unnamed: D28.3 (K2), U22.2 (OUT1)
unnamed: J10.3, RL1.3
unnamed: J10.4, RL1.4
unnamed: J11.3, RL2.3
unnamed: J11.4, RL2.4
unnamed: R62.2, R63.1, U21.2 (FB)
unnamed: R64.2, U22.31 (IREF)
unnamed: R66.2, U24.3 (IN1)
unnamed: R67.2, U24.4 (IN2)
unnamed: R68.2, U24.6 (IN3)
unnamed: R69.2, U24.7 (IN4)
unnamed: R70.1, U24.1 (TM)
unnamed: R70.2, R71.2, U24.2 (GND)
unnamed: R72.2, RL1.2
unnamed: R73.2, RL2.2
SCL: U22.29 (SCL), U23.12 (SCL); also elsewhere on the board
SDA: U22.28 (SDA), U23.13 (SDA); also elsewhere on the board
VLED: C60.1, D13.2 (A1), D14.2 (A1), D14.4 (A2), D16.4 (A2), D17.4 (A2), D18.4 (A2), D19.4 (A2), D20.4 (A2), D21.4 (A2), D22.2 (A1), D22.4 (A2), D23.2 (A1), D23.4 (A2), D24.2 (A1), D24.4 (A2), D25.2 (A1), D25.4 (A2), D26.2 (A1), D26.4 (A2), D27.2 (A1), D27.4 (A2), D28.2 (A1), D28.4 (A2), R62.1, U21.4 (VOUT), U21.6 (VOS); also elsewhere on the board
VSW1: U24.8 (VOUT4); also elsewhere on the board

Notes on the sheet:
Output
(27) OUT1
(28) COM1
(29) GND
(30) +12V
(26) GND
(25) AL+
Alarm
(32) COM2
(34) +12V
(33) GND
(31) OUT2
To PhotoEye
GRN
RED
Motor (Green=Opening, Red=Closing)
Open Limit (Green)
VLED Switcher (3.3V)
Address 010 1000
Address 010 0000
High-Side Switch
Shadow (Green=Active, Red=Error)
Safety (Green=Active, Red=Error)
Edge (Green=Active, Red=Error)
Close Limit (Green)
Close PhotoEye (Green=Active, Red=Error)
Open PhotoEye (Green=Active, Red=Error)
Stop (Green)
Close (Green)
Open (Green)
Pushbutton (Green)
Halt (Red)
Input 1 (Green=Active, Red=Error)
Input 2 (Green=Active, Red=Error)
30mA = 2.49k 25mA = 2.94k 20mA = 3.74k 15mA = 4.87k 10mA = 7.32k
All IC’s
Description
Current
288uA
Idle Currents
